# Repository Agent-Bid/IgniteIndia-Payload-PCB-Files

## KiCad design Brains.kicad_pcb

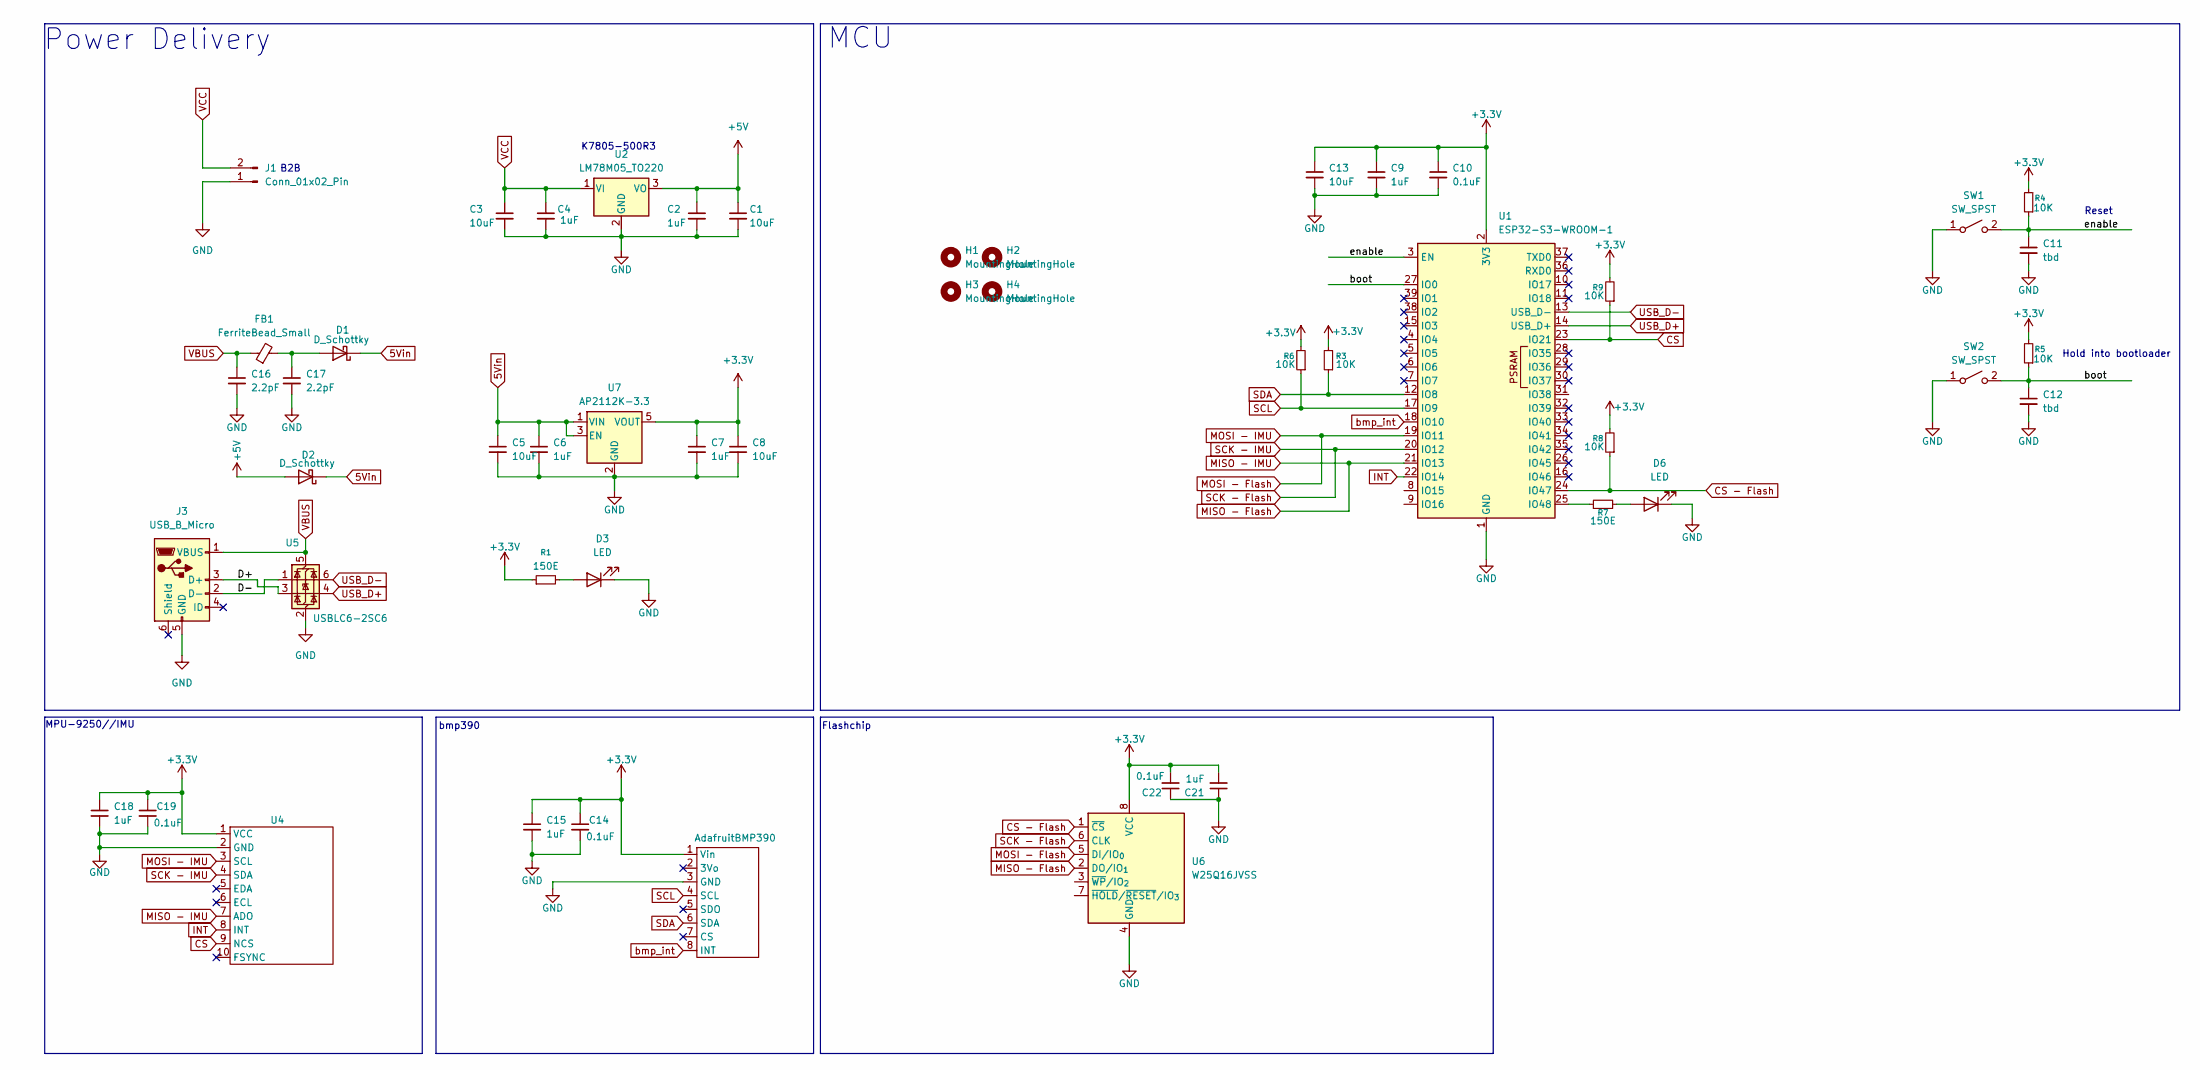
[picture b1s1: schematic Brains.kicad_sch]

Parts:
AdafruitBMP390: Adafruit BMP390Module
C1, C3, C5, C8, C13: 10uF; C_0603_1608Metric
C2, C4, C6, C7, C9, C15, C18, C21: 1uF; C_0603_1608Metric
C10, C14, C19, C22: 0.1uF; C_0603_1608Metric
C11, C12: tbd; C_0603_1608Metric
C16, C17: 2.2pF; C_0603_1608Metric
D1, D2: D_Schottky; D_1206_3216Metric
D3, D6: LED; LED_0603_1608Metric
FB1: FerriteBead_Small; L_0603_1608Metric
H1, H2, H3, H4: MountingHole; MountingHole_3.2mm_M3
J1: Conn_01x02_Pin; PinHeader_1x02_P2.54mm_Vertical
J3: USB_B_Micro; USB_Micro-B_Wuerth_629105150521
R1, R7: 150E; R_0603_1608Metric
R3, R4, R5, R6, R8, R9: 10K; R_0603_1608Metric
SW1, SW2: SW_SPST; SW_PUSH_6mm
U1: ESP32-S3-WROOM-1
U2: LM78M05_TO220; TO-220-3_Vertical
U4: Untitled
U5: USBLC6-2SC6; SOT-23-6
U6: W25Q16JVSS; SOIC-8_5.3x5.3mm_P1.27mm
U7: AP2112K-3.3; SOT-23-5

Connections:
5Vin: C5.1, C6.1, D1.1 (K), D2.1 (K), U7.1 (VIN), U7.3 (EN)
+3.3V: AdafruitBMP390.1 (Vin), C7.1, C8.1, C9.1, C10.1, C13.1, C14.1, C15.1, C18.1, C19.1, C21.2, C22.2, R1.1, R3.2, R4.2, R5.2, R6.2, R8.2, R9.2, U1.2 (3V3), U4.1 (VCC), U6.8 (VCC), U7.5 (VOUT)
+5V: C1.1, C2.1, D2.2 (A), U2.3 (VO)
/D+: J3.3 (D+), U5.3 (I/O2)
/D-: J3.2 (D-), U5.1 (I/O1)
/boot: C12.1, R5.1, SW2.2 (B), U1.27 (IO0)
/enable: C11.1, R4.1, SW1.2 (B), U1.3 (EN)
CS: R9.1, U1.23 (IO21), U4.9 (NCS)
CS - Flash: R8.1, U1.24 (IO47), U6.1 (~CS)
GND: AdafruitBMP390.3 (GND), C1.2, C2.2, C3.2, C4.2, C5.2, C6.2, C7.2, C8.2, C9.2, C10.2, C11.2, C12.2, C13.2, C14.2, C15.2, C16.2, C17.2, C18.2, C19.2, C21.1, C22.1, D3.1 (K), D6.1 (K), J1.1, J3.5 (GND), SW1.1 (A), SW2.1 (A), U1.1 (GND), U1.40 (GND), U1.41 (GND), U2.2 (GND), U4.2 (GND), U5.2 (GND), U6.4 (GND), U7.2 (GND)
INT: U1.22 (IO14), U4.8 (INT)
MISO - Flash: U1.21 (IO13), U4.7 (ADO), U6.2 (DO/IO_{1})
MOSI - Flash: U1.19 (IO11), U4.3 (SCL), U6.5 (DI/IO_{0})
unnamed: C17.1, D1.2 (A), FB1.2
unnamed: D3.2 (A), R1.2
unnamed: D6.2 (A), R7.2
unnamed: R7.1, U1.25 (IO48)
SCK - Flash: U1.20 (IO12), U4.4 (SDA), U6.6 (CLK)
SCL: AdafruitBMP390.4 (SCL), R6.1, U1.17 (IO9)
SDA: AdafruitBMP390.6 (SDA), R3.1, U1.12 (IO8)
USB_D+: U1.14 (USB_D+), U5.4 (I/O2)
USB_D-: U1.13 (USB_D-), U5.6 (I/O1)
VBUS: C16.1, FB1.1, J3.1 (VBUS), U5.5 (VBUS)
VCC: C3.1, C4.1, J1.2, U2.1 (VI)
bmp_int: AdafruitBMP390.8 (INT), U1.18 (IO10)

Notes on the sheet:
B2B
bmp390
MPU-9250//IMU
K7805-500R3
Flashchip
MCU
Power Delivery
Reset
Hold into bootloader

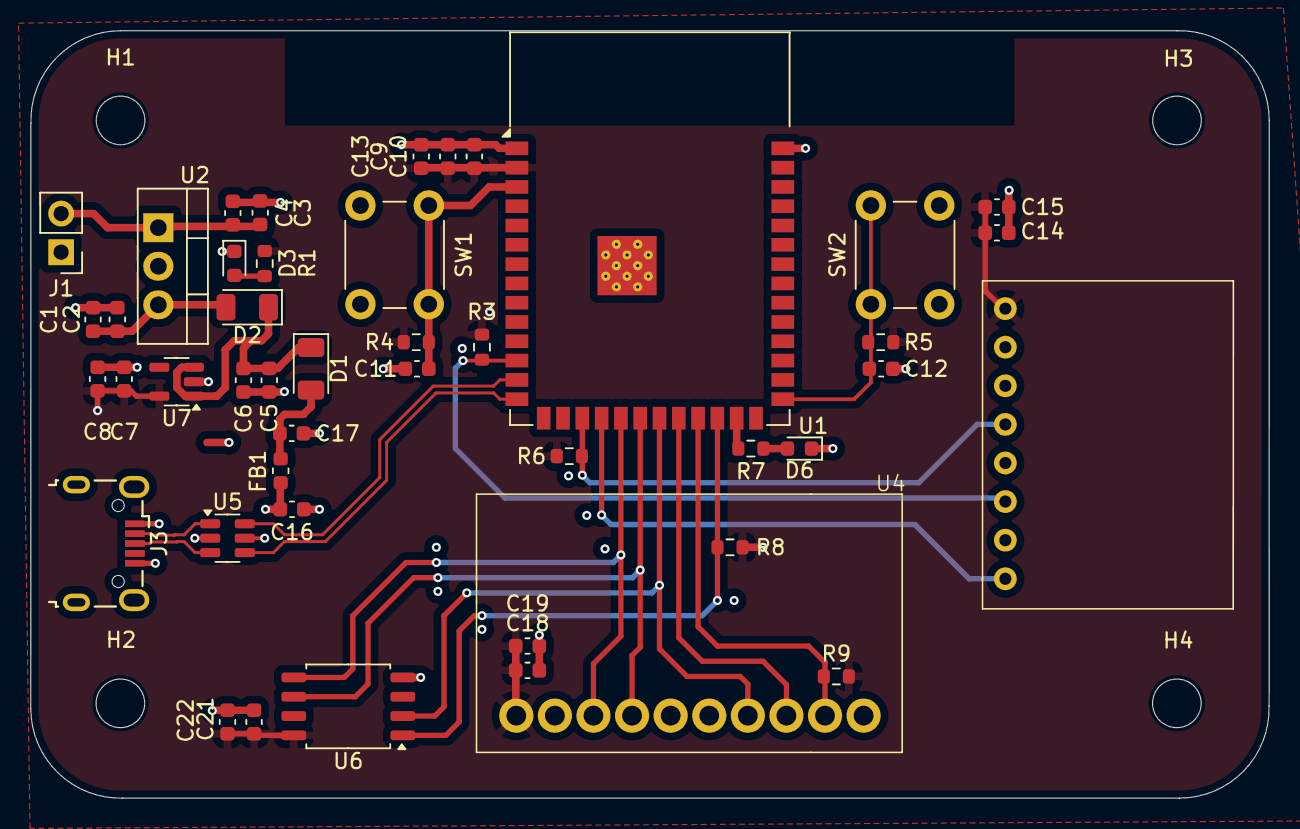
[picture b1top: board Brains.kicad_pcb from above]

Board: 4 copper layers, 81.5 x 50.5 mm, 49 parts (0 on the bottom side), 25 nets.

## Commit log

2025-09-02 Impedance Matching Left on USB
2025-09-02 Changed LDO to AP2112K-3.3, Updated Layout
